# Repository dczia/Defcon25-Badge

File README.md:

## DC-Zia 2017
Badge - Arduino 101 Shield with LCD Display, Neopixel Lights and Cherry MX Blue Keyboard Buttons

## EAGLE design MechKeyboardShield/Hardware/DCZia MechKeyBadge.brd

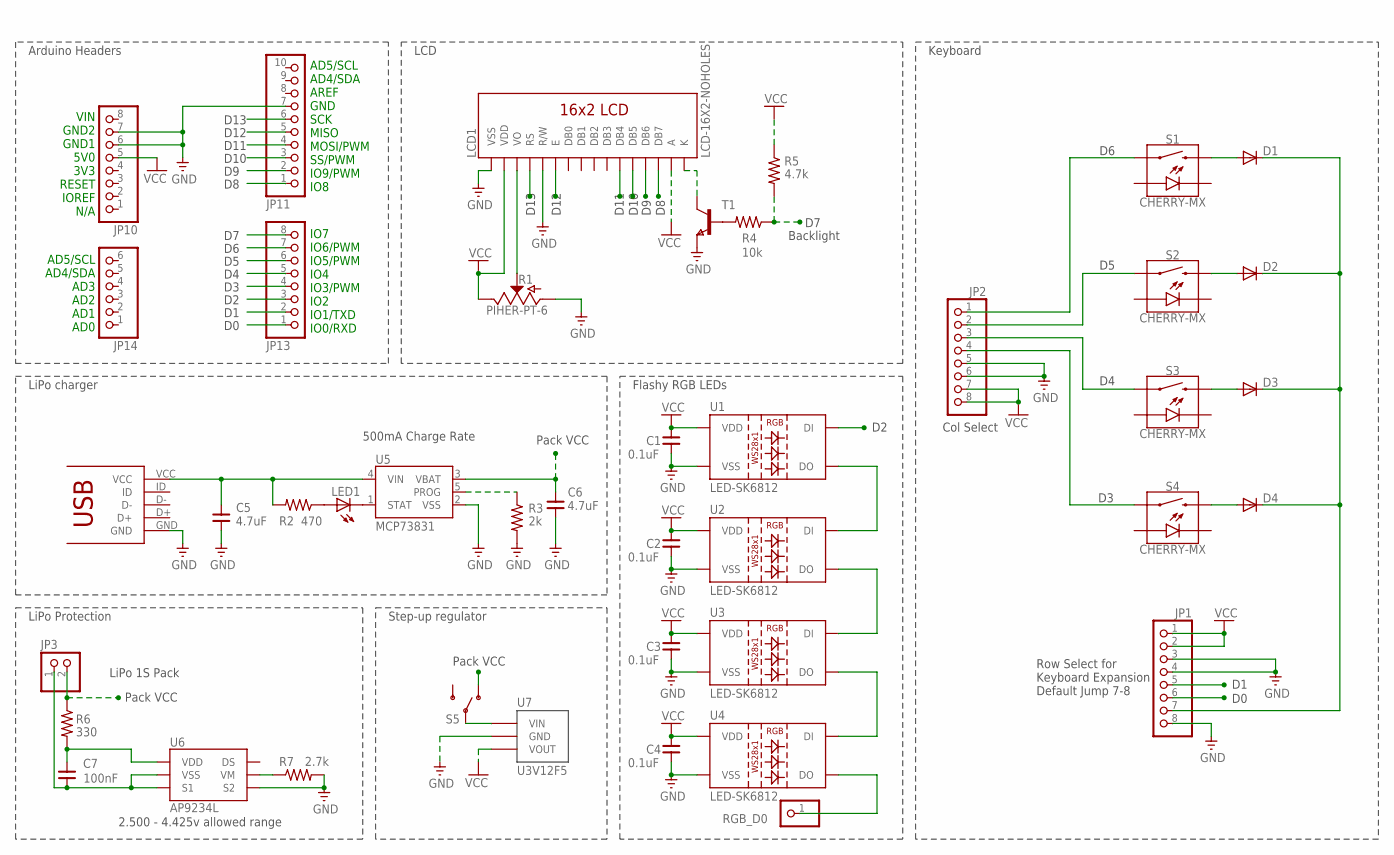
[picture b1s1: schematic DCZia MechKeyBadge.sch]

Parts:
C1, C2, C3, C4: 0.1uF; 1206
C5, C6: 4.7uF; 1206
C7: 100nF; 1206
D1, D2, D3, D4: DIODE-SOD123; SOD123
JP1, JP2, JP10, JP13: PINHD-1X8; 1X08
JP3: PINHD-1X2; 1X02
JP11: PINHD-1X10; 1X10
JP14: PINHD-1X6; 1X06
LCD1: LCD-16X2-NOHOLES; LCD-16X2
LED1: LEDSMT1206; 1206
R1: PIHER-PT-6
R2: 470; R1206
R3: 2k; R1206
R4: 10k; R1206
R5: 4.7k; R1206
R6: 330; R1206
R7: 2.7k; R1206
RGB_D0: PINHD-1X1; 1X01
S1, S2, S3, S4: CHERRY-MX; CHERRY-MX-LED
S5: SWITCH-SPDTSMD; SWITCH_SPDT_SMD
T1: NPNSOT23; SOT-23
U1, U2, U3, U4: LED-SK6812; SK6812
U5: MCP73831; SOT23-5
U6: AP9234L; U-DFN2535-6
U7: U3V12F5; POLOLU_REGULATOR
U$1: 10118192-0001LF

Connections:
D0: JP1.6, JP13.1
D1: JP1.5, JP13.2
D2: JP13.3, U1.P$2 (DI)
D3: JP2.4, JP13.4, S4.S1 (1)
D4: JP2.3, JP13.5, S3.S1 (1)
D5: JP2.2, JP13.6, S2.S1 (1)
D6: JP2.1, JP13.7, S1.S1 (1)
D7: JP13.8, R4.1, R5.2
D8: JP11.1, LCD1.14 (DB7)
D9: JP11.2, LCD1.13 (DB6)
D10: JP11.3, LCD1.12 (DB5)
D11: JP11.4, LCD1.11 (DB4)
D12: JP11.5, LCD1.6 (E)
D13: JP11.6, LCD1.4 (RS)
GND: C1.P$1 (1), C2.P$1 (1), C3.P$1 (1), C4.P$1 (1), C5.P$1 (1), C6.P$1 (1), JP1.3, JP1.4, JP1.8, JP2.5, JP2.6, JP10.6, JP10.7, JP11.7, LCD1.1 (VSS), LCD1.5 (R/W), R1.P$1 (1), R3.2, R7.2, T1.2 (E), U1.P$1 (VSS), U2.P$1 (VSS), U3.P$1 (VSS), U4.P$1 (VSS), U5.2 (VSS), U6.S2, U7.2 (GND), U$1.GND
unnamed: LCD1.3 (VO), R1.P$2 (2)
unnamed: U1.P$4 (DO), U2.P$2 (DI)
unnamed: U2.P$4 (DO), U3.P$2 (DI)
unnamed: U3.P$4 (DO), U4.P$2 (DI)
unnamed: D4.A, S4.S2 (2)
unnamed: D1.A, S1.S2 (2)
unnamed: D2.A, S2.S2 (2)
unnamed: D3.A, S3.S2 (2)
unnamed: LED1.A, R2.1
unnamed: LED1.C, U5.1 (STAT)
unnamed: R3.1, U5.5 (PROG)
unnamed: RGB_D0.1, U4.P$4 (DO)
unnamed: D1.C, D2.C, D3.C, D4.C, JP1.7
unnamed: R4.2, T1.3 (B)
unnamed: LCD1.16 (K), T1.1 (C)
unnamed: S5.2, U7.3 (VIN)
unnamed: C5.P$2 (2), R2.2, U5.4 (VIN), U$1.VCC
unnamed: R7.1, U6.VM
unnamed: C7.P$2 (2), JP3.1, U6.S1, U6.VSS
unnamed: C7.P$1 (1), R6.2, U6.VDD
PACK_VCC: C6.P$2 (2), JP3.2, R6.1, S5.1 (O), U5.3 (VBAT)
VCC: C1.P$2 (2), C2.P$2 (2), C3.P$2 (2), C4.P$2 (2), JP1.1, JP1.2, JP2.7, JP2.8, JP10.5, LCD1.2 (VDD), LCD1.15 (A), R1.P$3 (3), R5.1, U1.P$3 (VDD), U2.P$3 (VDD), U3.P$3 (VDD), U4.P$3 (VDD), U7.1 (VOUT)

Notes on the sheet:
VIN GND2 GND1 5V0 3V3 RESET IOREF N/A
AD5/SCL AD4/SDA AREF GND SCK MISO MOSI/PWM SS/PWM IO9/PWM IO8
IO7 IO6/PWM IO5/PWM IO4 IO3/PWM IO2 IO1/TXD IO0/RXD
AD5/SCL AD4/SDA AD3 AD2 AD1 AD0
D13
D12
D11
D10
Row Select for Keyboard Expansion Default Jump 7-8
Col Select
LiPo charger
Arduino Headers
Backlight
LCD
Flashy RGB LEDs
Keyboard
LiPo 1S Pack
Pack VCC
2.500 - 4.425v allowed range
LiPo Protection
500mA Charge Rate
Step-up regulator

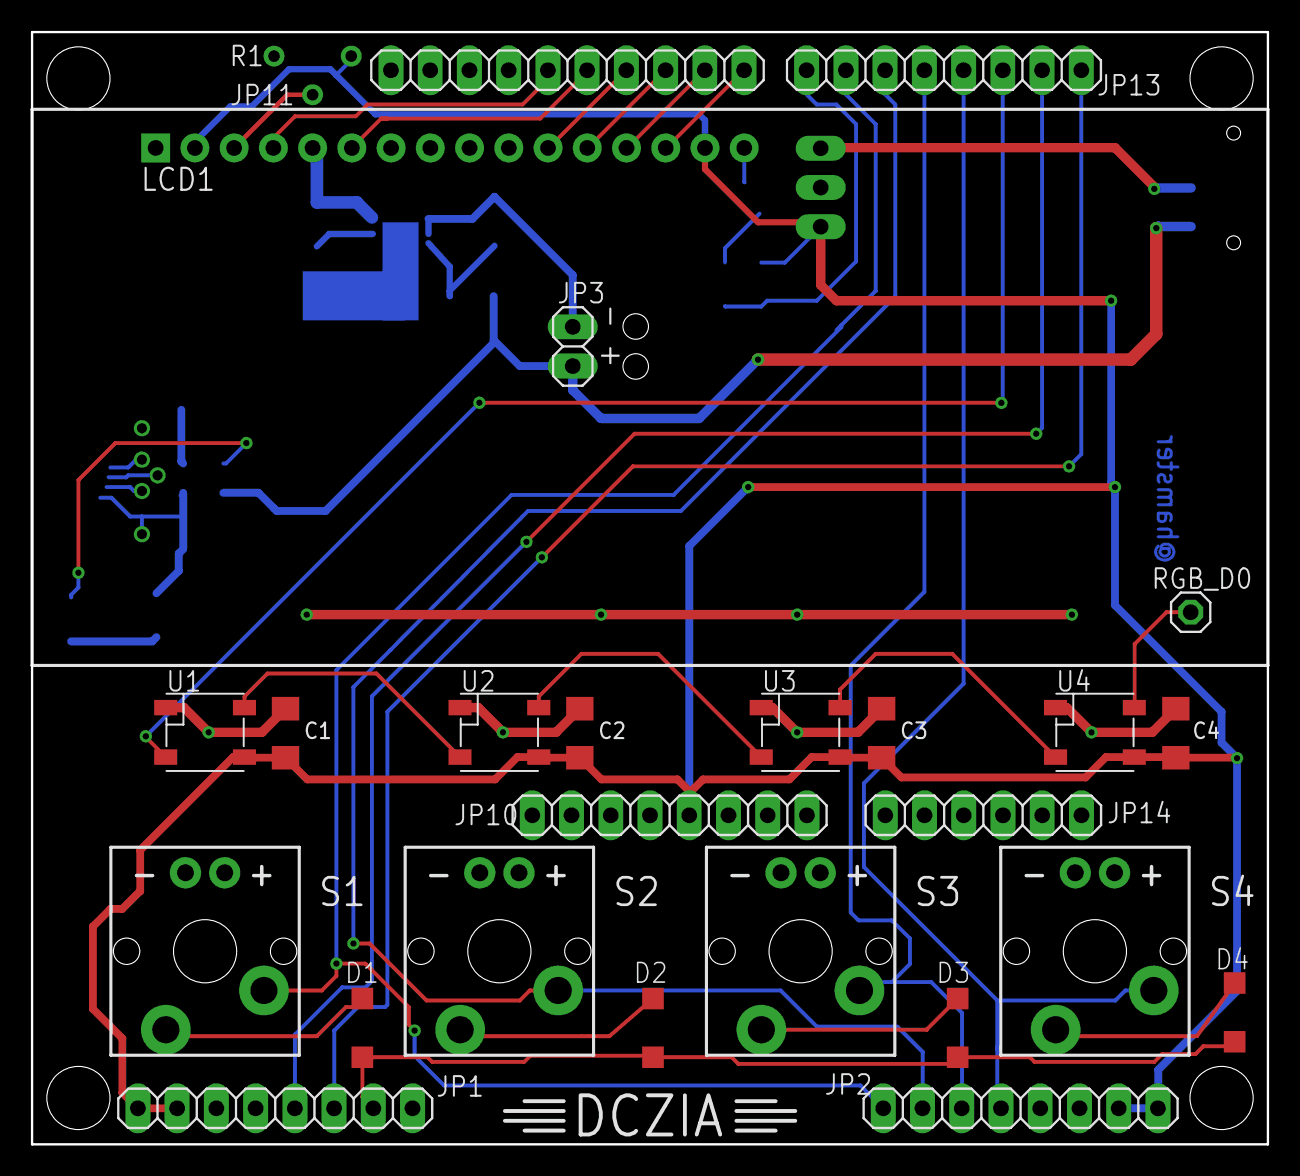
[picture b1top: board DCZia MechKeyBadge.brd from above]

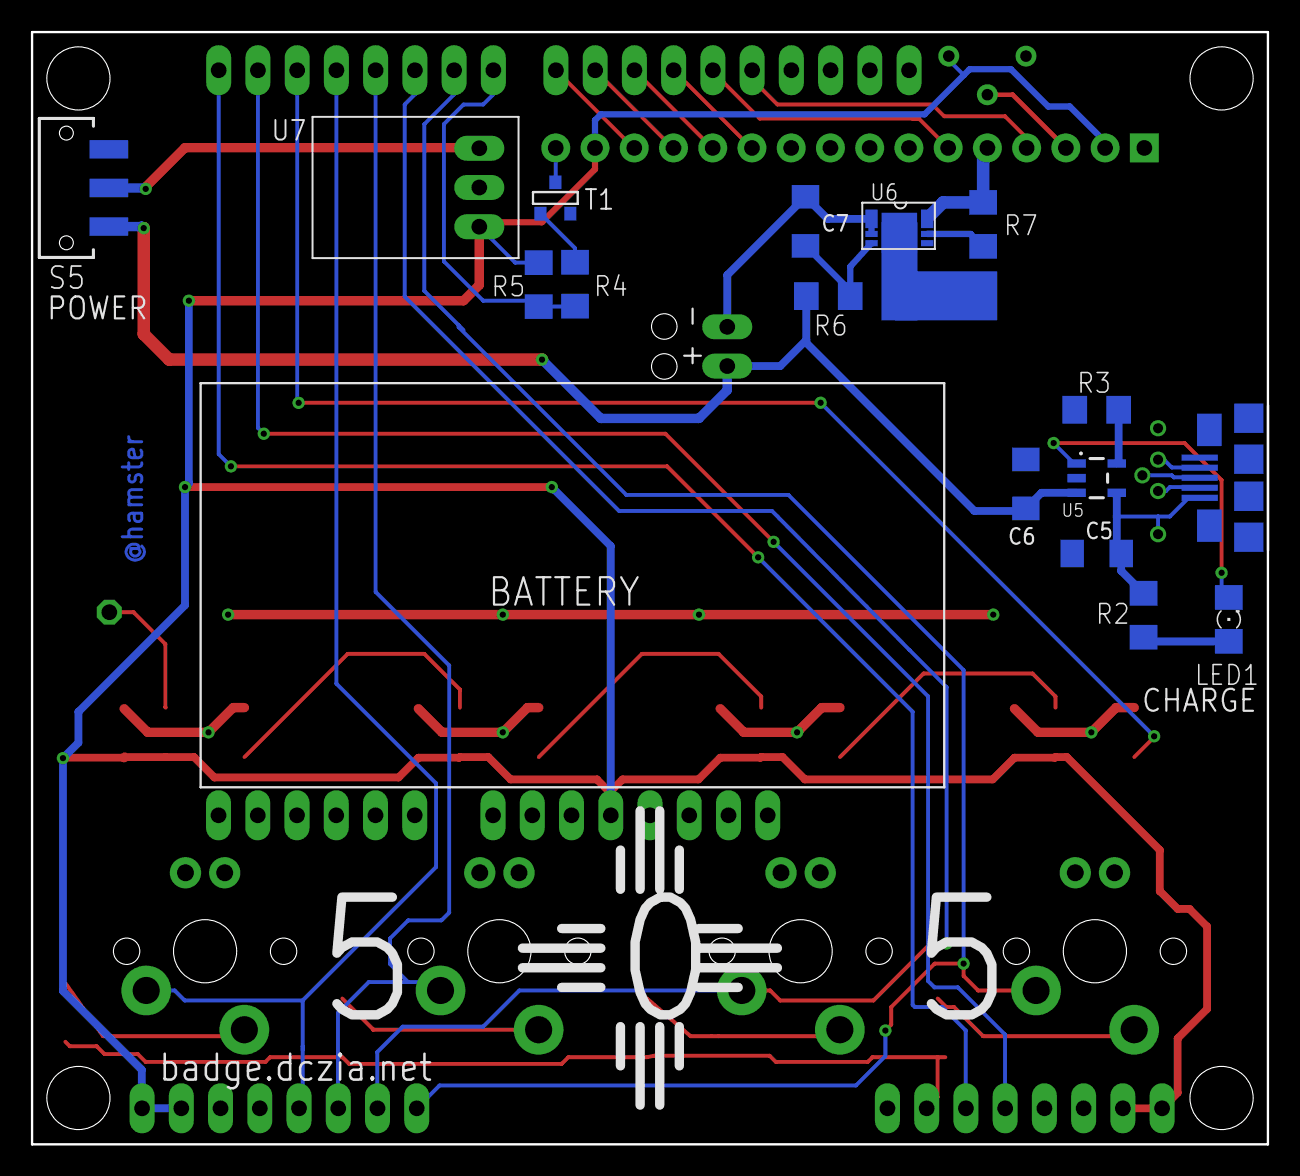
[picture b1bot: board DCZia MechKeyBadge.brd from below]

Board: 2 copper layers, 80.0 x 72.0 mm, 42 parts (16 on the bottom side), 37 nets.

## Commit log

2017-08-06 First commit containing all that's required to get the DCZia 2017 badge off the ground.
2017-08-06 Updates to readmes so they don't look bad.
2017-08-07 Moving software to new software folder
2017-08-07 Removed library files so Arduino won't be confused
2017-08-07 Adding hardware files Moved everything to a MechKeyboardShield directory
2017-08-07 Moved mechkeyboard software into mechkeyboardshield directory
2017-08-07 Fixed code block in readme

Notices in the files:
parts and their libraries:
SparkFun-IC-Power: Licensing: Creative Commons ShareAlike 4.0 International - https://creativecommons.org/licenses/by-sa/4.0
supply0: Copyright (C) 2007, Bob Starr
